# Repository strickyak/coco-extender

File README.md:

# coco-extender
Extension cards for Radio Shack Color Computers

Directory poor-yaks-mpi-2a is a simple PCB with 4 or 5 edgecard
sockets.  It does no buffering nor switching of signals,
so it is more like a "Y Cable" than like a real MPI.
But I find it useful!   See the README.md in that directory.

Directory coco-extender-v1/ is the older CoCoExBo by Rachel Keslensky.  It has
one Edgecard Female and one 40-pin header suitable for a 40-wire ribbon
cable, in addition to the edgecard male that inserts into the CoCo slot.
(Probably you should use the poor-yaks-mpi-2a/ PCB above, instead.)

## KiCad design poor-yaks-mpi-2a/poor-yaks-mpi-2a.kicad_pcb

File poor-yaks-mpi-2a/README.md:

# "Coco-Extender 2A" a.k.a. "A POOR YAK'S MPI"

NOTA BENE: This is not a consumer-friendly MPI.  It is more of an
experimenter's tool.  PLEASE READ THIS ENTIRE FILE so you will understand
the limitations!

This multi-slot Coco Extender is roughly a simple "Y cable" that brings
all the signals directly from the Coco's edgecard socket to up to five
edgecard slots.

All signals are ganged directly to the same pin number on all sockets,
with these exceptions:

* Pins 1 and 2, reserved for +12V and -12V, are never connected
    to anything.

* The +5V from the Coco is not wired to anything. 
    (Instead, you must provide an external +5VDC supply
    to the small connector in the corner, to power the
    +5V pins on the edgecard sockets.)

* /CTS and /SCS (that is, the active-low enables for Cartrige
    Rom and Floppy Disk controller) are wired to the first
    connector, and not to any others.   The others get +5V
    instead, the inactive voltage for these signals.

There is no buffering on this extender, so you may not be able to use
all the slots, without putting too large a load on your poor little Coco.

The Fifth slot could be used for a fifth edgecard socket, but I like to
solder pin headers on it, and use it as debug signals for an oscilloscope.

The 8-pin header in the lower right corner of the board is where you
must provide +5VDC from an external supply.  That will be the +5V to
all of the edgecard sockets (but not to the Coco itself!).  Here is
an example 3A 5VDC supply that is under $10 on Amazon that comes
with a plug adapter that is easy to wire to the power pin headers:
https://www.amazon.com/MTYTOT-Adapter-100V-240V-Converter-Security/dp/B0BV64MHY6/

This schematic has no surface mount components and needs no assembly by
the PCB maker.  But you'll have to get your own 40-pin edgecard sockets
and your own pin headers, and solder them on.

You can get 40-pin edgecard sockets from here:
https://www.amazon.com/dp/B0BPP35SRC

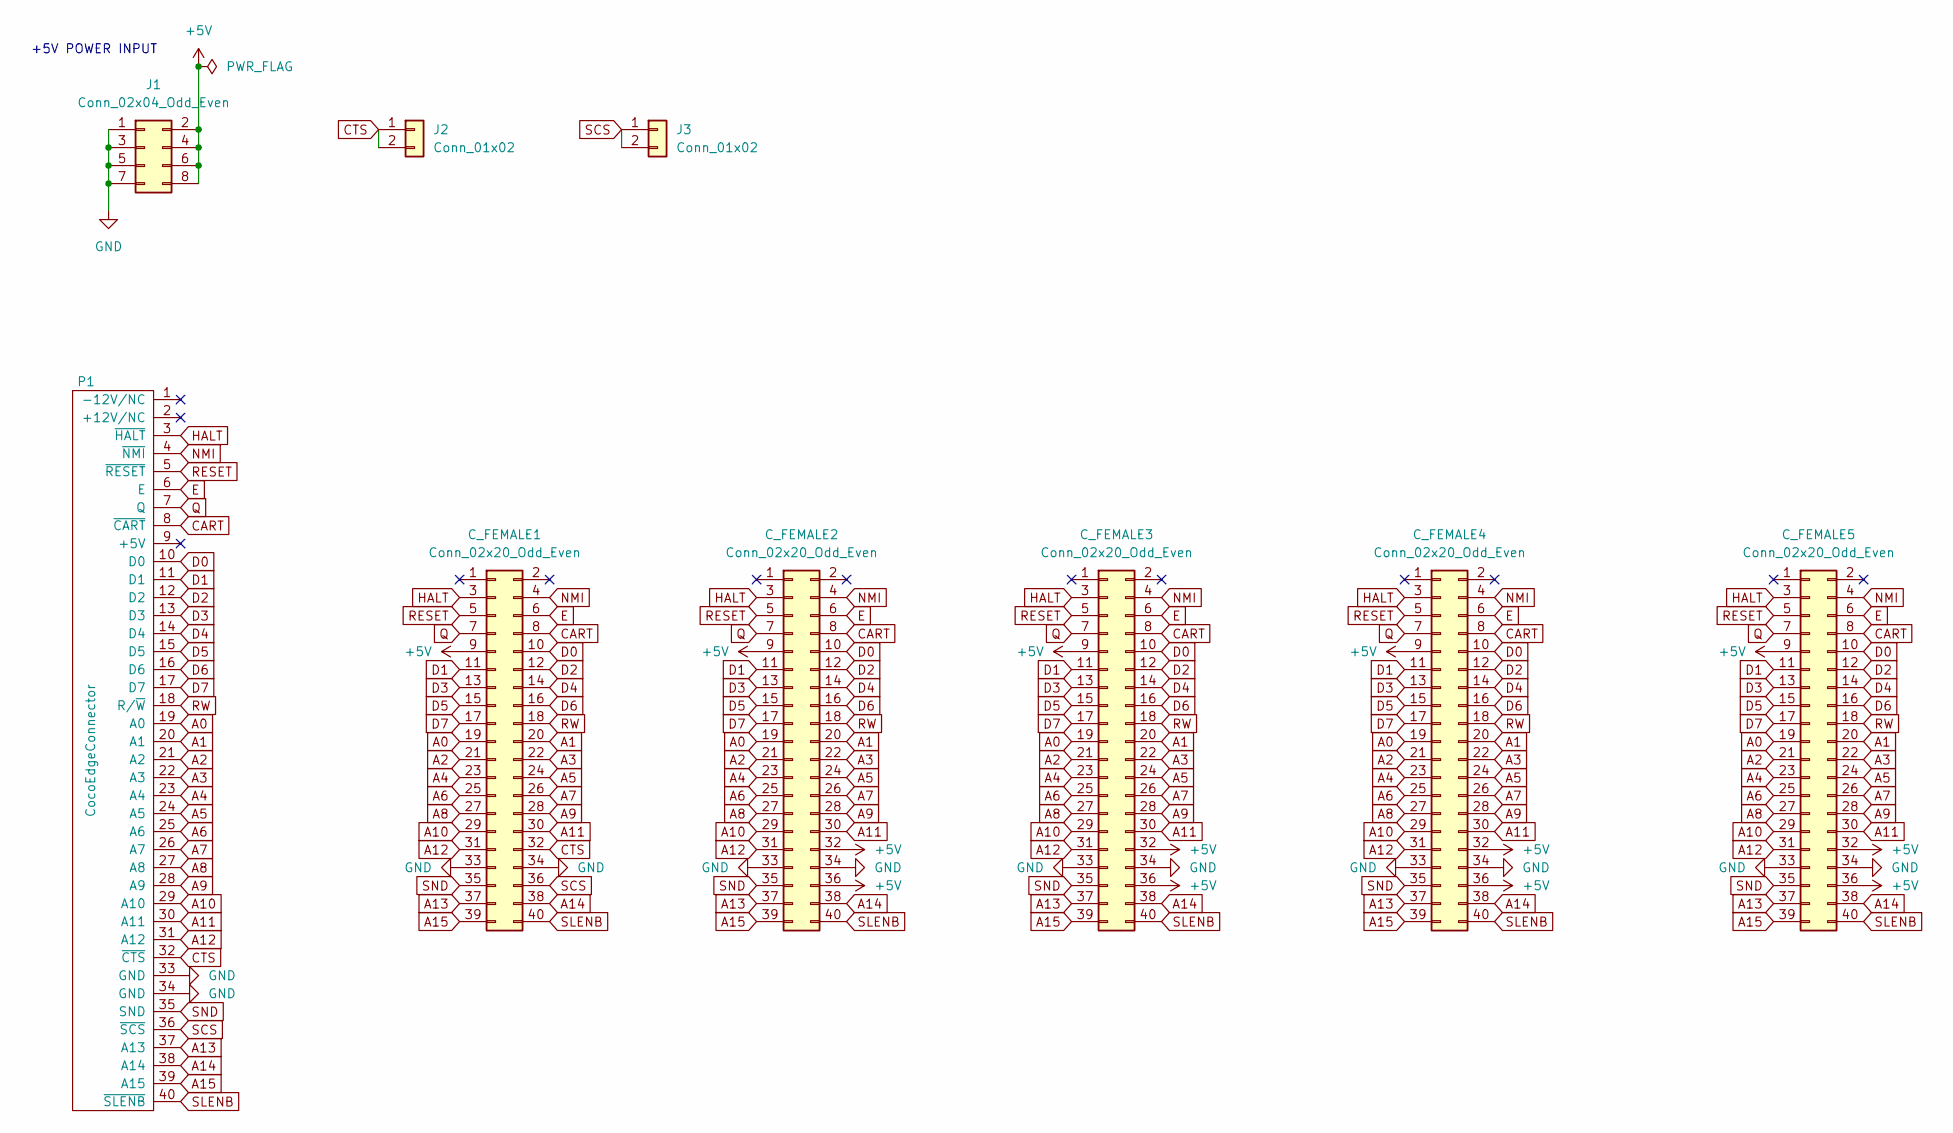
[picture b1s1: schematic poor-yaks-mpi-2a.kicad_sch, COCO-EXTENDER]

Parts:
C_FEMALE1, C_FEMALE2, C_FEMALE3, C_FEMALE4, C_FEMALE5: Conn_02x20_Odd_Even; Coco_Card_Female
J1: Conn_02x04_Odd_Even; PinHeader_2x04_P2.54mm_Vertical
J2, J3: Conn_01x02; PinHeader_1x02_P2.54mm_Vertical
P1: CocoEdgeConnector; CocoCardEdgeCocoMIDI

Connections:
+5V: C_FEMALE1.9, C_FEMALE2.9, C_FEMALE2.32, C_FEMALE2.36, C_FEMALE3.9, C_FEMALE3.32, C_FEMALE3.36, C_FEMALE4.9, C_FEMALE4.32, C_FEMALE4.36, C_FEMALE5.9, C_FEMALE5.32, C_FEMALE5.36, J1.2, J1.4, J1.6, J1.8
A0: C_FEMALE1.19, C_FEMALE2.19, C_FEMALE3.19, C_FEMALE4.19, C_FEMALE5.19, P1.19 (A0)
A1: C_FEMALE1.20, C_FEMALE2.20, C_FEMALE3.20, C_FEMALE4.20, C_FEMALE5.20, P1.20 (A1)
A2: C_FEMALE1.21, C_FEMALE2.21, C_FEMALE3.21, C_FEMALE4.21, C_FEMALE5.21, P1.21 (A2)
A3: C_FEMALE1.22, C_FEMALE2.22, C_FEMALE3.22, C_FEMALE4.22, C_FEMALE5.22, P1.22 (A3)
A4: C_FEMALE1.23, C_FEMALE2.23, C_FEMALE3.23, C_FEMALE4.23, C_FEMALE5.23, P1.23 (A4)
A5: C_FEMALE1.24, C_FEMALE2.24, C_FEMALE3.24, C_FEMALE4.24, C_FEMALE5.24, P1.24 (A5)
A6: C_FEMALE1.25, C_FEMALE2.25, C_FEMALE3.25, C_FEMALE4.25, C_FEMALE5.25, P1.25 (A6)
A7: C_FEMALE1.26, C_FEMALE2.26, C_FEMALE3.26, C_FEMALE4.26, C_FEMALE5.26, P1.26 (A7)
A8: C_FEMALE1.27, C_FEMALE2.27, C_FEMALE3.27, C_FEMALE4.27, C_FEMALE5.27, P1.27 (A8)
A9: C_FEMALE1.28, C_FEMALE2.28, C_FEMALE3.28, C_FEMALE4.28, C_FEMALE5.28, P1.28 (A9)
A10: C_FEMALE1.29, C_FEMALE2.29, C_FEMALE3.29, C_FEMALE4.29, C_FEMALE5.29, P1.29 (A10)
A11: C_FEMALE1.30, C_FEMALE2.30, C_FEMALE3.30, C_FEMALE4.30, C_FEMALE5.30, P1.30 (A11)
A12: C_FEMALE1.31, C_FEMALE2.31, C_FEMALE3.31, C_FEMALE4.31, C_FEMALE5.31, P1.31 (A12)
A13: C_FEMALE1.37, C_FEMALE2.37, C_FEMALE3.37, C_FEMALE4.37, C_FEMALE5.37, P1.37 (A13)
A14: C_FEMALE1.38, C_FEMALE2.38, C_FEMALE3.38, C_FEMALE4.38, C_FEMALE5.38, P1.38 (A14)
A15: C_FEMALE1.39, C_FEMALE2.39, C_FEMALE3.39, C_FEMALE4.39, C_FEMALE5.39, P1.39 (A15)
CART: C_FEMALE1.8, C_FEMALE2.8, C_FEMALE3.8, C_FEMALE4.8, C_FEMALE5.8, P1.8 (~CART)
CTS: C_FEMALE1.32, J2.1, J2.2, P1.32 (~CTS)
D0: C_FEMALE1.10, C_FEMALE2.10, C_FEMALE3.10, C_FEMALE4.10, C_FEMALE5.10, P1.10 (D0)
D1: C_FEMALE1.11, C_FEMALE2.11, C_FEMALE3.11, C_FEMALE4.11, C_FEMALE5.11, P1.11 (D1)
D2: C_FEMALE1.12, C_FEMALE2.12, C_FEMALE3.12, C_FEMALE4.12, C_FEMALE5.12, P1.12 (D2)
D3: C_FEMALE1.13, C_FEMALE2.13, C_FEMALE3.13, C_FEMALE4.13, C_FEMALE5.13, P1.13 (D3)
D4: C_FEMALE1.14, C_FEMALE2.14, C_FEMALE3.14, C_FEMALE4.14, C_FEMALE5.14, P1.14 (D4)
D5: C_FEMALE1.15, C_FEMALE2.15, C_FEMALE3.15, C_FEMALE4.15, C_FEMALE5.15, P1.15 (D5)
D6: C_FEMALE1.16, C_FEMALE2.16, C_FEMALE3.16, C_FEMALE4.16, C_FEMALE5.16, P1.16 (D6)
D7: C_FEMALE1.17, C_FEMALE2.17, C_FEMALE3.17, C_FEMALE4.17, C_FEMALE5.17, P1.17 (D7)
E: C_FEMALE1.6, C_FEMALE2.6, C_FEMALE3.6, C_FEMALE4.6, C_FEMALE5.6, P1.6 (E)
GND: C_FEMALE1.33, C_FEMALE1.34, C_FEMALE2.33, C_FEMALE2.34, C_FEMALE3.33, C_FEMALE3.34, C_FEMALE4.33, C_FEMALE4.34, C_FEMALE5.33, C_FEMALE5.34, J1.1, J1.3, J1.5, J1.7, P1.33 (GND), P1.34 (GND)
HALT: C_FEMALE1.3, C_FEMALE2.3, C_FEMALE3.3, C_FEMALE4.3, C_FEMALE5.3, P1.3 (~HALT)
NMI: C_FEMALE1.4, C_FEMALE2.4, C_FEMALE3.4, C_FEMALE4.4, C_FEMALE5.4, P1.4 (~NMI)
Q: C_FEMALE1.7, C_FEMALE2.7, C_FEMALE3.7, C_FEMALE4.7, C_FEMALE5.7, P1.7 (Q)
RESET: C_FEMALE1.5, C_FEMALE2.5, C_FEMALE3.5, C_FEMALE4.5, C_FEMALE5.5, P1.5 (~RESET)
RW: C_FEMALE1.18, C_FEMALE2.18, C_FEMALE3.18, C_FEMALE4.18, C_FEMALE5.18, P1.18 (R/~W)
SCS: C_FEMALE1.36, J3.1, J3.2, P1.36 (~SCS)
SLENB: C_FEMALE1.40, C_FEMALE2.40, C_FEMALE3.40, C_FEMALE4.40, C_FEMALE5.40, P1.40 (~SLENB)
SND: C_FEMALE1.35, C_FEMALE2.35, C_FEMALE3.35, C_FEMALE4.35, C_FEMALE5.35, P1.35 (SND)

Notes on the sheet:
+5V POWER INPUT

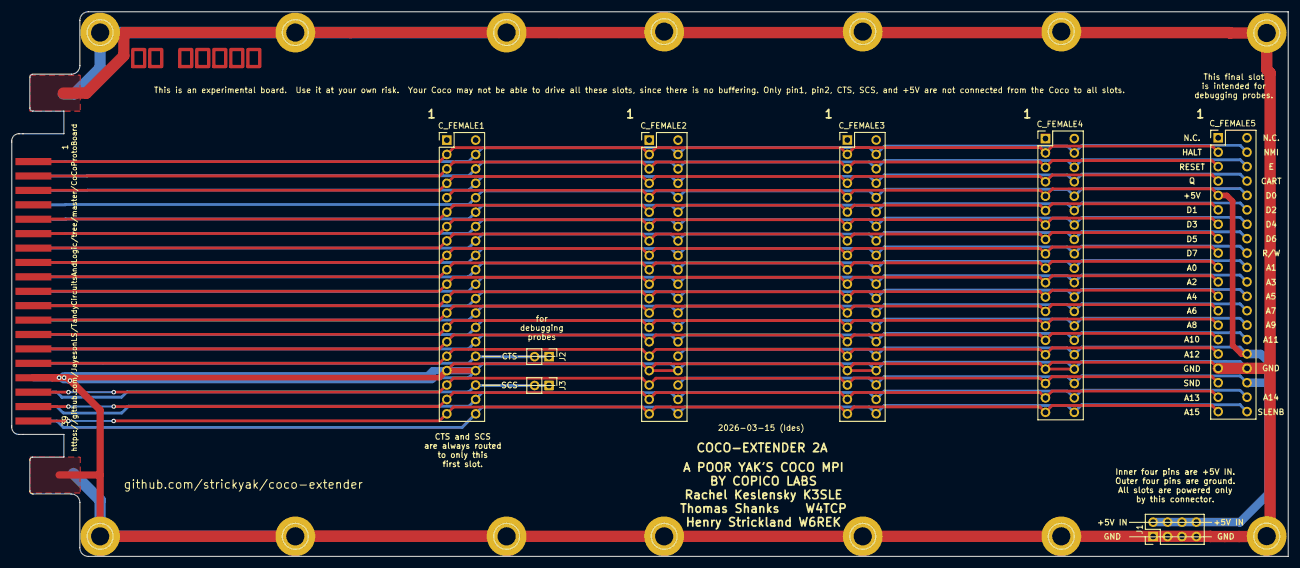
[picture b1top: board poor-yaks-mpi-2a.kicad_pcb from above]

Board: 2 copper layers, 225.0 x 96.0 mm, 9 parts (0 on the bottom side), 37 nets.

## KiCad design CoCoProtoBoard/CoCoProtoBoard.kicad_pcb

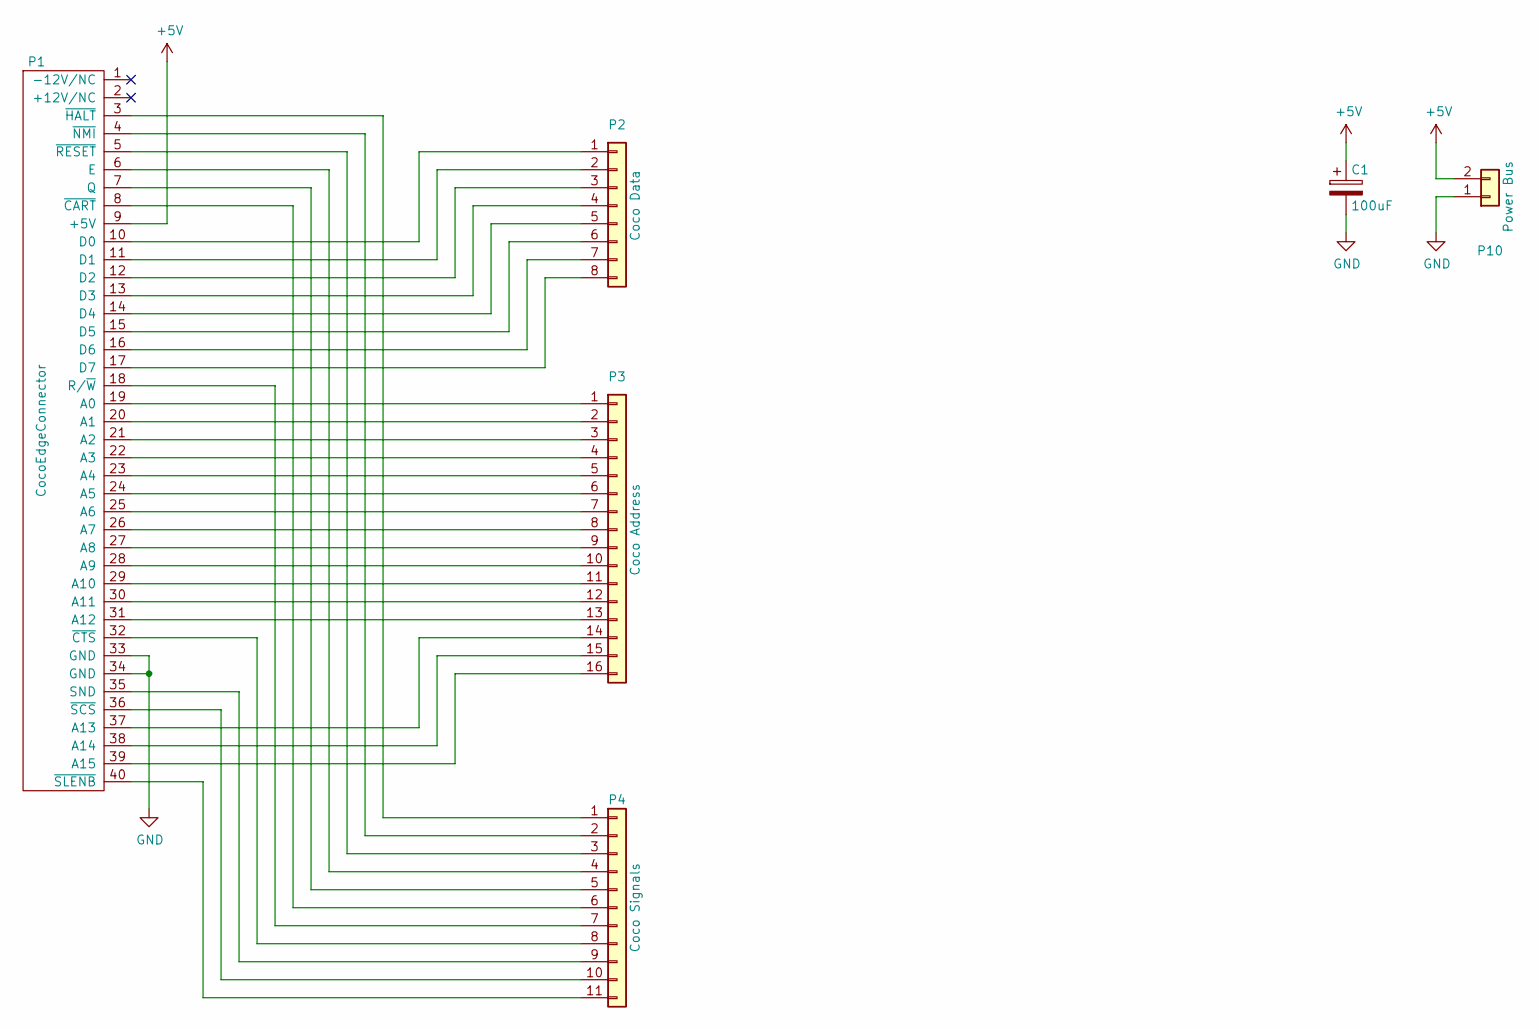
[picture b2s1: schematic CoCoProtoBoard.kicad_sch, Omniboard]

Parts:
C1: 100uF; C_Radial_D7.5_L11.2_P2.5
P1: CocoEdgeConnector; CocoCardEdge
P2: Coco Data; DIP-16_W7.62mm
P3: Coco Address; DIP-32_W15.24mm
P4: Coco Signals; DIP-22_W10.16mm
P10: Power Bus; DIP-16_W7.62mm

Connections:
+5V: C1.1, P1.9 (+5V), P10.2
unnamed: P1.3 (~HALT), P4.1
unnamed: P1.4 (~NMI), P4.2
unnamed: P1.5 (~RESET), P4.3
unnamed: P1.6 (E), P4.4
unnamed: P1.7 (Q), P4.5
unnamed: P1.8 (~CART), P4.6
unnamed: P1.10 (D0), P2.1
unnamed: P1.11 (D1), P2.2
unnamed: P1.12 (D2), P2.3
unnamed: P1.13 (D3), P2.4
unnamed: P1.14 (D4), P2.5
unnamed: P1.15 (D5), P2.6
unnamed: P1.16 (D6), P2.7
unnamed: P1.17 (D7), P2.8
unnamed: P1.18 (R/~W), P4.7
unnamed: P1.19 (A0), P3.1
unnamed: P1.20 (A1), P3.2
unnamed: P1.21 (A2), P3.3
unnamed: P1.22 (A3), P3.4
unnamed: P1.23 (A4), P3.5
unnamed: P1.24 (A5), P3.6
unnamed: P1.25 (A6), P3.7
unnamed: P1.26 (A7), P3.8
unnamed: P1.27 (A8), P3.9
unnamed: P1.28 (A9), P3.10
unnamed: P1.29 (A10), P3.11
unnamed: P1.30 (A11), P3.12
unnamed: P1.31 (A12), P3.13
unnamed: P1.32 (~CTS), P4.8
unnamed: P1.35 (SND), P4.9
unnamed: P1.36 (~SCS), P4.10
unnamed: P1.37 (A13), P3.14
unnamed: P1.38 (A14), P3.15
unnamed: P1.39 (A15), P3.16
unnamed: P1.40 (~SLENB), P4.11

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
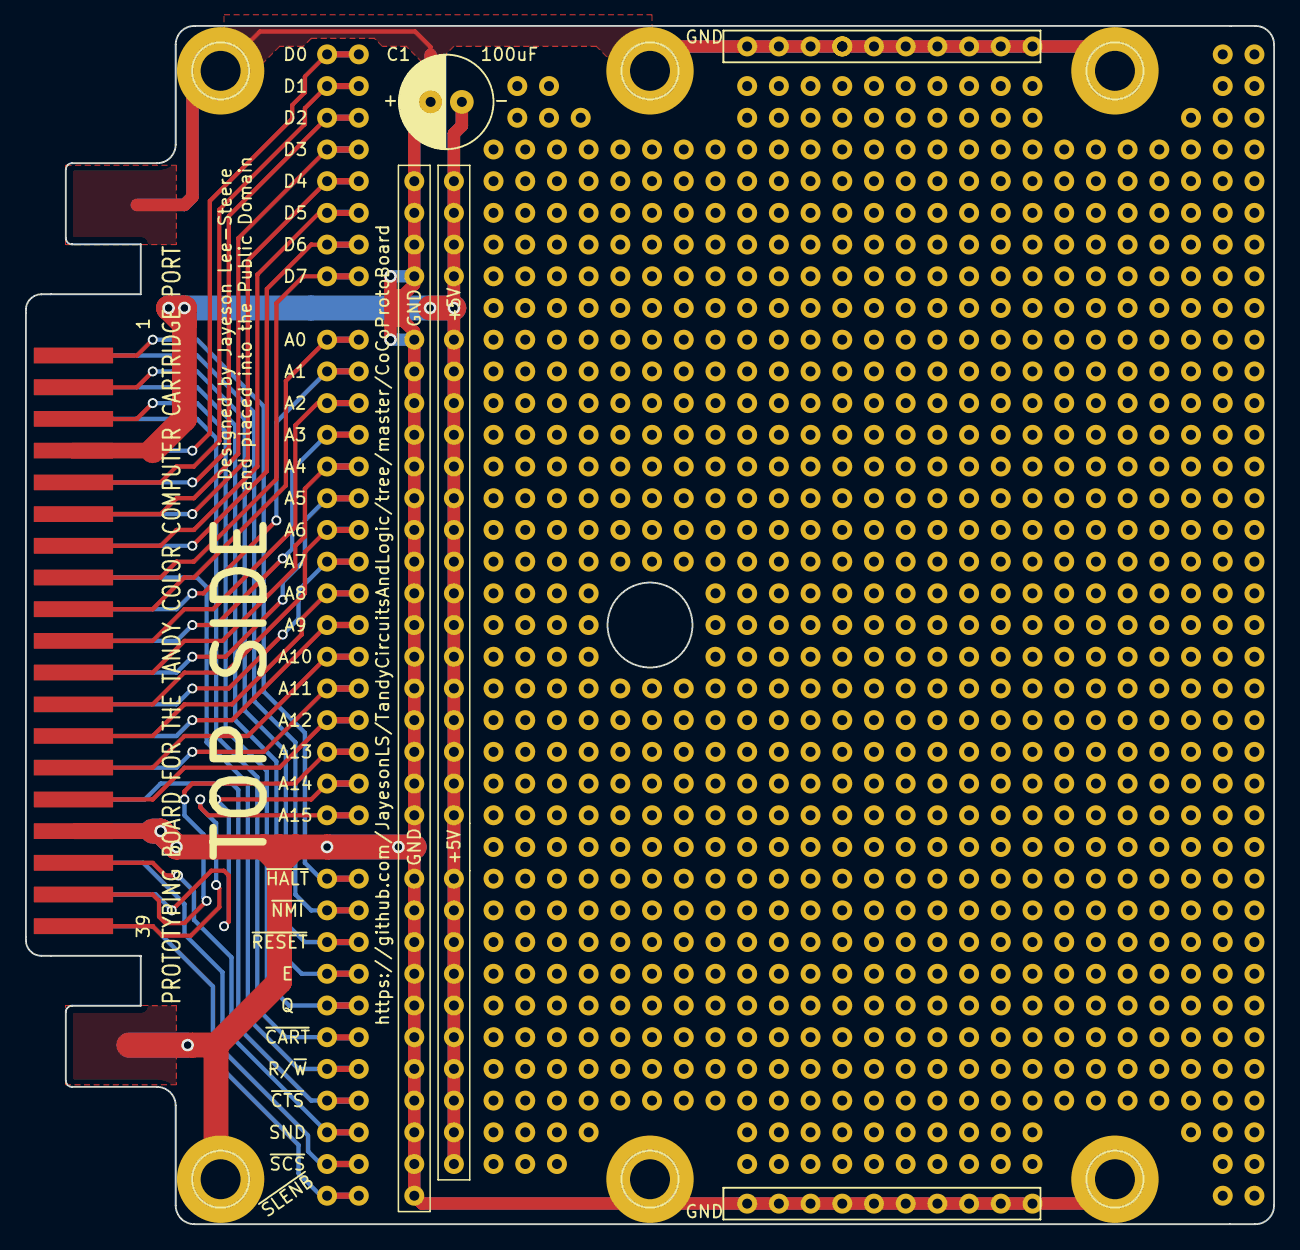
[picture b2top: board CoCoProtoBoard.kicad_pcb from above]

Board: 2 copper layers, 100.0 x 96.0 mm, 6 parts (0 on the bottom side), 37 nets.

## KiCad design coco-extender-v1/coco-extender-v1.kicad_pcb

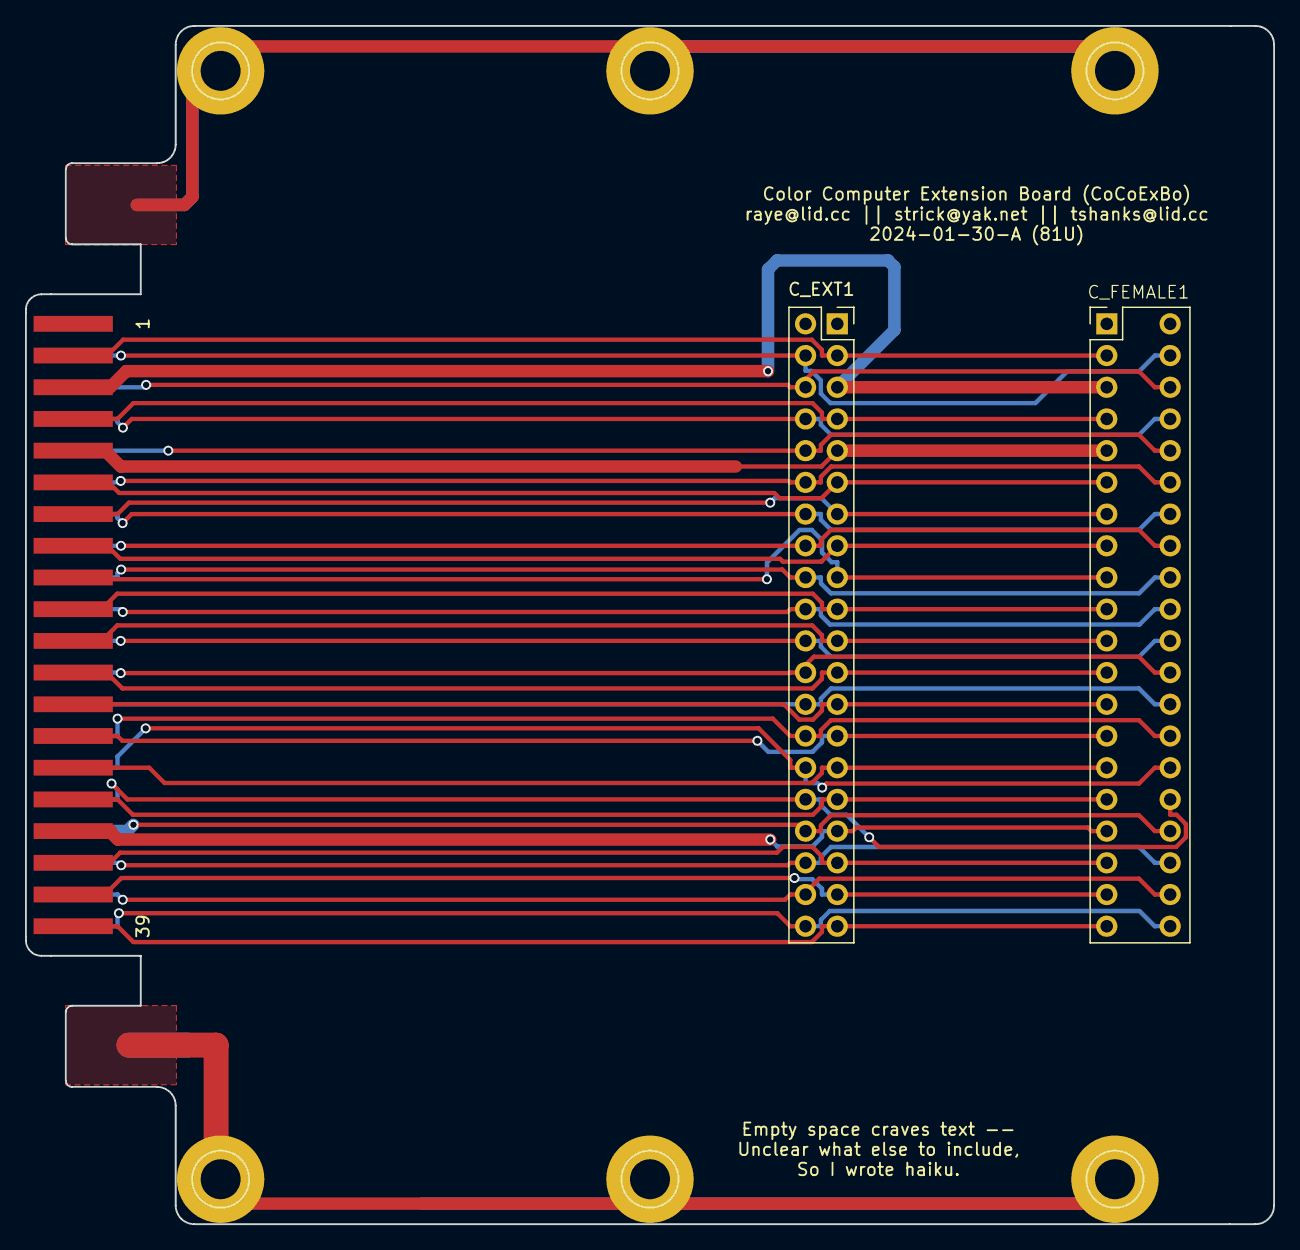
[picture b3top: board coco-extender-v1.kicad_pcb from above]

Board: 2 copper layers, 100.0 x 96.0 mm, 9 parts (0 on the bottom side), 39 nets.

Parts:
CMALE1: Conn_02x20_Odd_Even; CocoCardEdge
C_EXT1: Conn_02x20_Odd_Even; PinSocket_2x20_P2.54mm_Vertical
C_FEMALE1: Conn_02x20_Odd_Even; Coco_Card_Female
GND1, GND2, GND3, GND4, GND5, GND6: 1pin

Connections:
/a3: CMALE1.3, C_EXT1.3, C_FEMALE1.3
/a4: CMALE1.4, C_EXT1.4, C_FEMALE1.4
/a5: CMALE1.5, C_EXT1.5, C_FEMALE1.5
/a6: CMALE1.6, C_EXT1.6, C_FEMALE1.6
/a7: CMALE1.7, C_EXT1.7, C_FEMALE1.7
/a8: CMALE1.8, C_EXT1.8, C_FEMALE1.8
/a9: CMALE1.9, C_EXT1.9, C_FEMALE1.9
/a10: CMALE1.10, C_EXT1.10, C_FEMALE1.10
/a11: CMALE1.11, C_EXT1.11, C_FEMALE1.11
/a12: CMALE1.12, C_EXT1.12, C_FEMALE1.12
/a13: CMALE1.13, C_EXT1.13, C_FEMALE1.13
/a14: CMALE1.14, C_EXT1.14, C_FEMALE1.14
/a15: CMALE1.15, C_EXT1.15, C_FEMALE1.15
/a16: CMALE1.16, C_EXT1.16, C_FEMALE1.16
/a17: CMALE1.17, C_EXT1.17, C_FEMALE1.17
/a18: CMALE1.18, C_EXT1.18, C_FEMALE1.18
/a19: CMALE1.19, C_EXT1.19, C_FEMALE1.19
/a20: CMALE1.20, C_EXT1.20, C_FEMALE1.20
/a21: CMALE1.21, C_EXT1.21, C_FEMALE1.21
/a22: CMALE1.22, C_EXT1.22, C_FEMALE1.22
/a23: CMALE1.23, C_EXT1.23, C_FEMALE1.23
/a24: CMALE1.24, C_EXT1.24, C_FEMALE1.24
/a25: CMALE1.25, C_EXT1.25, C_FEMALE1.25
/a26: CMALE1.26, C_EXT1.26, C_FEMALE1.26
/a27: CMALE1.27, C_EXT1.27, C_FEMALE1.27
/a28: CMALE1.28, C_EXT1.28, C_FEMALE1.28
/a29: CMALE1.29, C_EXT1.29, C_FEMALE1.29
/a30: CMALE1.30, C_EXT1.30, C_FEMALE1.30
/a31: CMALE1.31, C_EXT1.31, C_FEMALE1.31
/a32: CMALE1.32, C_EXT1.32, C_FEMALE1.32
/a33: CMALE1.33, C_EXT1.33, C_FEMALE1.33
/a34: CMALE1.34, C_EXT1.34, C_FEMALE1.34
/a35: CMALE1.35, C_EXT1.35, C_FEMALE1.35
/a36: CMALE1.36, C_EXT1.36, C_FEMALE1.36
/a37: CMALE1.37, C_EXT1.37, C_FEMALE1.37
/a38: CMALE1.38, C_EXT1.38, C_FEMALE1.38
/a39: CMALE1.39, C_EXT1.39, C_FEMALE1.39
/a40: CMALE1.40, C_EXT1.40, C_FEMALE1.40
GND: GND1.1, GND2.1, GND3.1, GND4.1, GND5.1, GND6.1

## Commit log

2024-03-15 add old coco-extender-v1
2024-03-15 LICENSE names
2024-03-15 CoCoProtoBoard, the physical basis of our boards.
2026-03-28 coco-extender 2A (a.k.a. poor-yaks-mpi)
2026-03-28 Update README and add an image.
2026-03-28 where to get 40-pin sockets

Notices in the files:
CoCoProtoBoard/CoCoProtoBoard.kicad_pcb:
and placed into the Public Domain
